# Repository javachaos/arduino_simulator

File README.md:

# arduino_simulator

`arduino_simulator` is a standalone AVR simulation and board-tooling workspace.

https://javachaos.github.io/arduino_simulator/

## License

This workspace is licensed under the GNU General Public License, version 3
or later. See `LICENSE`.

## Current Layout

The workspace is now split cleanly by responsibility:

- `rust_cpu/`
  Native AVR instruction-set simulator
- `rust_mcu/`
  Native ATmega328P / ATmega2560 MMIO and board-facing runtime layers
- `rust_board/`
  Native board DSL, KiCad import, and layout geometry
- `rust_project/`
  Native document model for projects, boards, modules, and hierarchical assemblies
- `rust_behavior/`
  Native declarative behavior definitions plus compiled runtime behavior engines for reusable modules
- `rust_runtime/`
  Native CLI for running Mega/Nano firmware from Intel HEX
- `rust_gui/`
  Native desktop GUI for compile/load/run plus CPU and serial inspection
- `rust_kicad/`
  Native KiCad adapter for generating/syncing `.avrsim.json` projects from KiCad PCBs
- `kicad_plugin/`
  Thin KiCad PCB action plugin that launches the Rust KiCad adapter from inside PCB Editor

The checked-in workspace is Rust-only. Board parsing, built-in models, layout
geometry, and document formats now live in the Rust crates.

## Native Runtime

Run Nano firmware:

```sh
cargo run -p rust_runtime -- run-nano /path/to/firmware.hex
```

Run Mega firmware:

```sh
cargo run -p rust_runtime -- run-mega /path/to/firmware.hex
```

Launch the native terminal monitor:

```sh
cargo run -p rust_runtime -- monitor-mega /path/to/firmware.hex
```

## Native GUI

Launch the desktop GUI:

```sh
cargo run -p rust_gui
```

The GUI can:

- compile an Arduino `.ino` sketch with `arduino-cli`
- load a `.hex` image directly
- open and save simulation project JSON documents
- open a dedicated board editor for authoring multi-PCB board-stack files
- keep the selected host board, firmware source, and PCB path together
- load board-definition JSON documents and render their primary PCB-backed member directly
- edit and persist host signal to PCB net bindings
- load multiple PCB-backed board/module members into one assembly bundle
- associate optional `Mega` / `Nano` host boards plus `.ino` / `.hex` firmware per member
- associate built-in or file-backed runtime behaviors with reusable sensor/interface modules
- wire member ports together and save the result as an `assembly_bundle` board file
- open a bidirectional serial console window with host baud selection
- run, pause, step, reset, and clear serial output
- show CPU state, registers, next instruction, compile log, and scrollable serial output

The GUI and project crates use `rust_board` for KiCad import, built-in board
models, and layout rendering.

For the least-friction auto-wiring and live net highlighting, keep your PCB net
names aligned with the selected Arduino board. In practice that means using the
same Arduino-facing signal names where possible, such as `D22`, `D50_MISO`, or
`A10`, or the official MCU-port names used by that board design, such as
`PA0`, `PC6`, or `PK2` on a Mega 2560.

## KiCad Plugin

If you want one-click launch behavior from KiCad PCB Editor, install the action
plugin:

```sh
python3 /Users/fred/Documents/arduino_simulator/kicad_plugin/install_kicad_plugin.py
```

Then use:

- `Tools -> External Plugins -> Open Arduino Simulator`

The plugin now offers:

- `Generic PCB mode` for opening any KiCad board directly in the GUI
- `Arduino simulation project` mode for `.avrsim.json` generation, firmware,
  and host-board binding workflows

## Rust Workspace

Run the native test suites from the workspace root:

```sh
cargo test -p rust_cpu
cargo test -p rust_mcu
cargo test -p rust_board
cargo test -p rust_project
cargo test -p rust_runtime
cargo test -p rust_gui
cargo test -p rust_kicad
```

Or run everything:

```sh
cargo test
```

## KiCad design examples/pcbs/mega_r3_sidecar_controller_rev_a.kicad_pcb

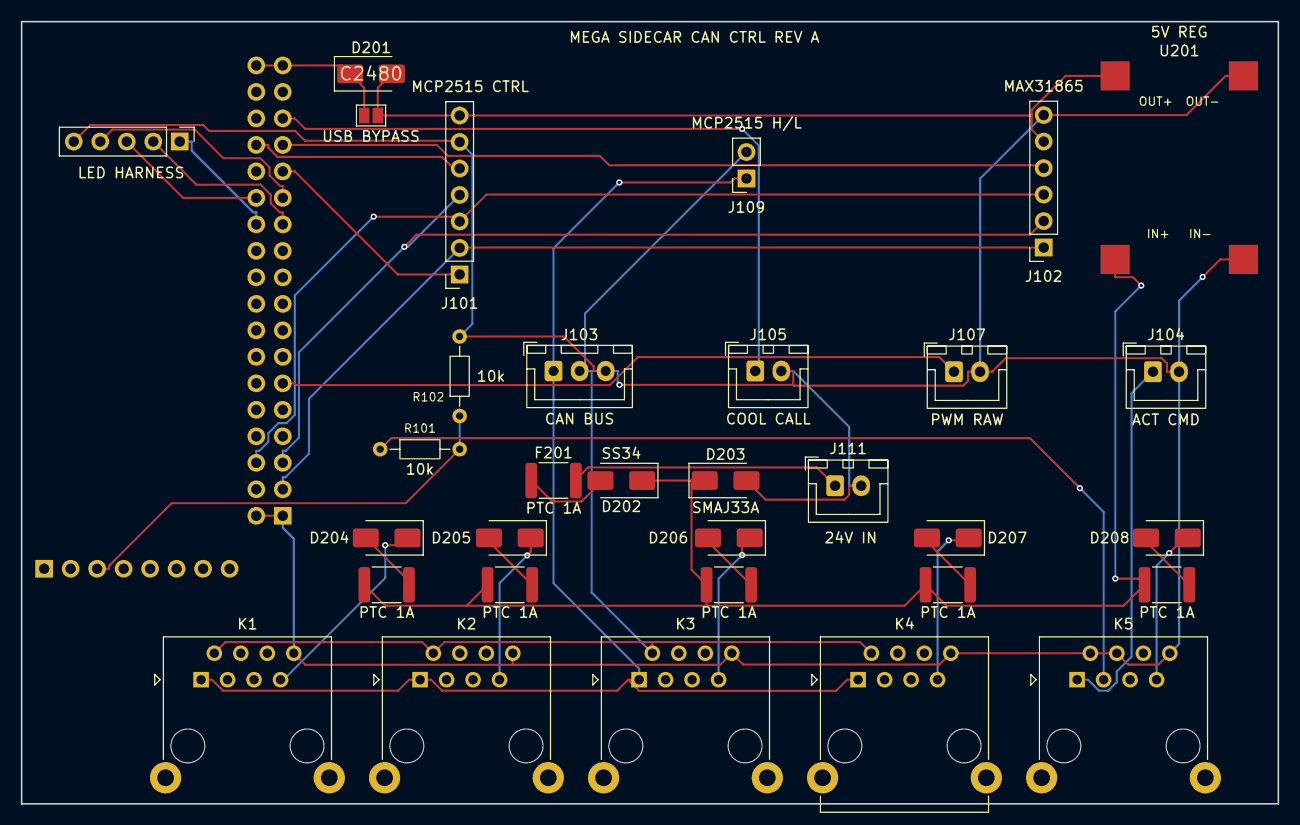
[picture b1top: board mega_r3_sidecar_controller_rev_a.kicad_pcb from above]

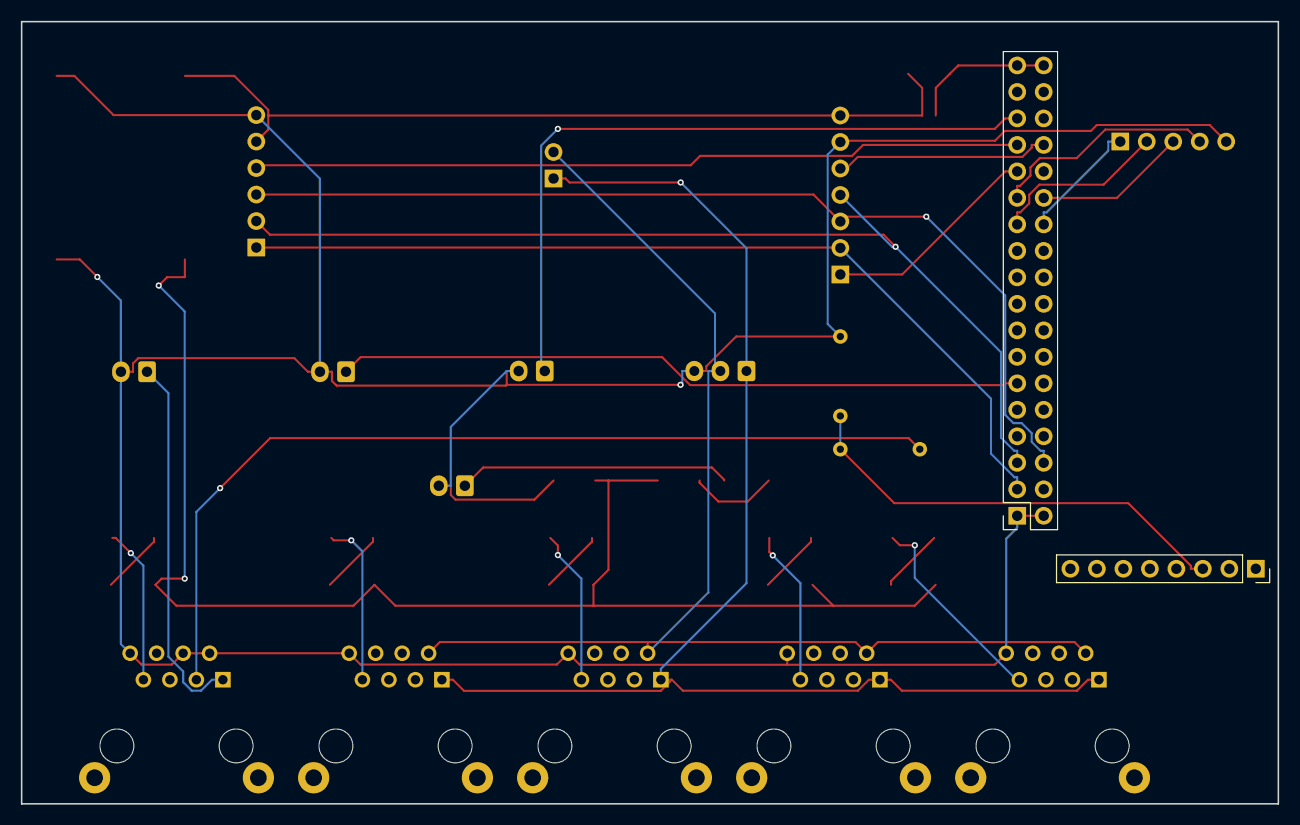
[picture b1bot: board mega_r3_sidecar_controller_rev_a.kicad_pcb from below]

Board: 2 copper layers, 120.5 x 75.0 mm, 34 parts (2 on the bottom side), 33 nets.

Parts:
D201, D204, D205, D206, D207, D208: SS14; D_SMA
D202: SS34; D_SMA
D203: SMAJ33A; D_SMA
F201, F202, F203, F204, F205, F206: PTC 1A; Fuse_1812_4532Metric
J101: MCP2515 CTRL; PinSocket_1x07_P2.54mm_Vertical
J102: MAX31865; PinSocket_1x06_P2.54mm_Vertical
J103: CAN BUS; JST_XH_B3B-XH-A_1x03_P2.50mm_Vertical
J104: ACT CMD; JST_XH_B2B-XH-A_1x02_P2.50mm_Vertical
J105: COOL CALL; JST_XH_B2B-XH-A_1x02_P2.50mm_Vertical
J106: LED HARNESS; PinHeader_1x05_P2.54mm_Vertical
J107: PWM RAW; JST_XH_B2B-XH-A_1x02_P2.50mm_Vertical
J109: MCP2515 H/L; PinSocket_1x02_P2.54mm_Vertical
J111: 24V IN; JST_XH_B2B-XH-A_1x02_P2.50mm_Vertical
K1: AIR Z1; RJ45_RCH_RC01937
K2: AIR Z2; RJ45_RCH_RC01937
K3: AIR Z3; RJ45_RCH_RC01937
K4: AIR SPARE; RJ45_RCH_RC01937
K5: ACTUATOR; RJ45_RCH_RC01937
P_AUX: MEGA A8-A15; PinHeader_1x08_P2.54mm_Vertical
P_DIG: MEGA D22-D53; PinHeader_2x18_P2.54mm_Vertical
R101, R102: 10k; R_Axial_DIN0204_L3.6mm_D1.6mm_P7.62mm_Horizontal
SJ201: USB BYPASS; SolderJumper-2_P1.3mm_Open_Pad1.0x1.5mm
U201: 5V REG MOD; Regulator_Module_12.3x17.6mm

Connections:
+5V: D201.2, J101.7, J102.5, SJ201.2, U201.3
/ACT_U_RAW: K5.3, R101.1
/ADC10: P_AUX.3, R101.2, R102.1
/PA3: J105.1, P_DIG.31
/PA4: J101.5, P_DIG.30
/PA5: J102.4, P_DIG.29
/PA7: J101.1, P_DIG.27
/PB0: J101.2, J102.1, P_DIG.3
/PB2: J101.4, J102.2, P_DIG.5
/PB3: J101.3, J102.3, P_DIG.6
/PC4: J106.2, P_DIG.23
/PC5: J106.1, P_DIG.24
/PC6: J106.4, P_DIG.25
/PC7: J106.3, P_DIG.26
/PL4: J107.1, P_DIG.11
ACT_Y_CMD: J104.1, K5.1
CANH: J103.1, J109.1, K1.1, K2.1, K3.1, K4.1
CANL: J103.2, J109.2, K1.2, K2.2, K3.2, K4.2
FIELD_24V: D202.1, D203.1, F202.1, F203.1, F204.1, F205.1, F206.1, U201.1
GND: D203.2, J101.6, J102.6, J103.3, J104.2, J105.2, J106.5, J107.2, J111.2, K1.8, K2.8, K3.8, K4.8, K5.2, K5.4, K5.8, P_DIG.1, P_DIG.2, R102.2, U201.2, U201.4
K1_24V: D204.1, K1.7
K1_24V_FUSED: D204.2, F202.2
K2_24V: D205.1, K2.7
K2_24V_FUSED: D205.2, F203.2
K3_24V: D206.1, K3.7
K3_24V_FUSED: D206.2, F204.2
K4_24V: D207.1, K4.7
K4_24V_FUSED: D207.2, F205.2
K5_24V: D208.1, K5.7
K5_24V_FUSED: D208.2, F206.2
MEGA_5V: D201.1, P_DIG.35, P_DIG.36, SJ201.1
VIN_FUSED_24V: D202.2, F201.1
VIN_RAW_24V: F201.2, J111.1

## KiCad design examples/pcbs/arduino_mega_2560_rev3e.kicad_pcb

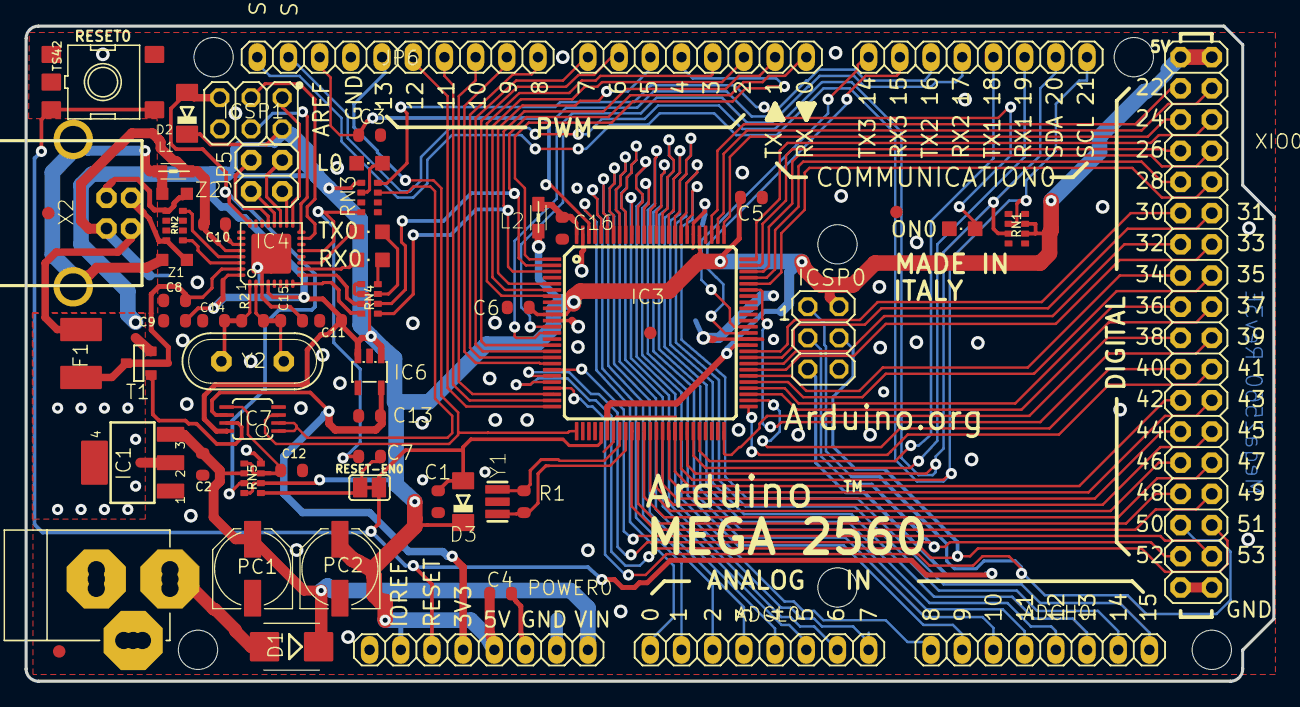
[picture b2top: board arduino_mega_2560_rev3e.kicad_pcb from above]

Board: 2 copper layers, 101.6 x 53.3 mm, 72 parts (1 on the bottom side), 111 nets.

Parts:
ADCH0: FH254-108DF08500V; 1X08
ADCL0: FH254-108DF08500V; 1X08
C1, C14, C15: 22p; C0603-ROUND
C2, C3, C4, C5, C6, C7, C8, C9, C11, C12, C16: 100nF; C0603-ROUND
C10, C13: 1uF; C0603-ROUND
COMMUNICATION0: FH254-108DF08500V; 1X08
D1: M7; SMB
D2, D3: CD1206-S01575; MINIMELF
F1: MF-MSMF050-2 500mA; L1812
FD1, FD2, FD3, FD4: FIDUCIALMOUNT; FIDUCIA-MOUNT
GROUND0: SJ
IC1: 1870_LD1117S50CTR; LINEAR_SOT223
IC3: ATMEGA2560-15AU; TQFP100
IC4: ATMEGA16U2-MU; MLF32
IC6: LP2985-33DBVR; SOT23-DBV
IC7: LMV358IDGKR; MSOP08
ICSP0, ICSP1: ICSP; 2X03
JP5: 2x2M - NM; 2X02
JP6: FH254-110DF08500V; 1X10
L0: Yellow; CHIPLED_0805
L1: MH2029-300Y; 0805
L2: 10uH; 0805
ON0: Green; CHIPLED_0805
PC1, PC2: 47uF; PANASONIC_D
POWER0: FH254-108DF08500V; 1X08
PWML0: FH254-108DF08500V; 1X08
R1, R2: 1M; R0603-ROUND
RESET0: TS42
RESET-EN0: SJ
RN1, RN5: 10k; CAY16
RN2: 22R; CAY16
RN3, RN4: 1K; CAY16
RX0: Yellow; CHIPLED_0805
T1: PMV48XP; SOT-23
TX0: Yellow; CHIPLED_0805
U$1, U$2: DNP; FRAME
UNK_HOLE_0: dummyfp0
UNK_HOLE_1: dummyfp1
UNK_HOLE_2: dummyfp2
UNK_HOLE_3: dummyfp3
UNK_HOLE_4: dummyfp4
UNK_HOLE_5: dummyfp5
X1: POWERSUPPLY_DC21MMX; POWERSUPPLY_DC-21MM
X2: PN61729
XIO0: 18x2F-H8.5; 2X18
Y1: CSTCE16M0V53-R0; RESONATOR
Y2: 16MHz; QS
Z1, Z2: BRNCG0603MLC-05E; CT_CN0603

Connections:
8PB4: IC4.18, JP5.1
8PB5: IC4.19, JP5.3
8PB6: IC4.20, JP5.2
8PB7: IC4.21, JP5.4
+3V3: C13.2, IC6.5, IC7.6, POWER0.4
+5V: C4.1, C5.1, C6.1, C9.1, C11.2, D2.C, D3.C, IC1.2, IC1.4, IC3.10, IC3.31, IC3.61, IC3.80, IC4.4, IC4.32, IC6.1, IC6.3, IC7.8, ICSP0.2, ICSP1.2, L2.2, PC2.+, POWER0.2, POWER0.5, RN1.6, RN1.7, RN3.1, RN4.5, RN4.6, RN5.2, RN5.8, T1.2, XIO0.1, XIO0.2
ADC0: ADCL0.1, IC3.97
ADC1: ADCL0.2, IC3.96
ADC2: ADCL0.3, IC3.95
ADC3: ADCL0.4, IC3.94
ADC4: ADCL0.5, IC3.93
ADC5: ADCL0.6, IC3.92
ADC6: ADCL0.7, IC3.91
ADC7: ADCL0.8, IC3.90
ADC8: ADCH0.1, IC3.89
ADC9: ADCH0.2, IC3.88
ADC10: ADCH0.3, IC3.87
ADC11: ADCH0.4, IC3.86
ADC12: ADCH0.5, IC3.85
ADC13: ADCH0.6, IC3.84
ADC14: ADCH0.7, IC3.83
ADC15: ADCH0.8, IC3.82
AREF: C3.1, IC3.98, JP6.3
AVCC: C16.1, IC3.100, L2.1
CMP: C12.2, IC7.5, RN5.3, RN5.5
D+: RN2.5, X2.3, Z2.2
D-: RN2.8, X2.2, Z1.2
DTR: C7.1, IC4.13, RN3.4
GATE_CMD: IC7.7, T1.3
GND: C1.2, C2.2, C3.2, C4.2, C5.2, C6.2, C8.2, C9.2, C11.1, C12.1, C13.1, C14.2, C15.2, C16.2, GROUND0.2, IC1.1, IC3.11, IC3.32, IC3.62, IC3.81, IC3.99, IC4.3, IC4.33, IC6.2, IC7.4, ICSP0.6, ICSP1.6, JP6.4, L0.C, ON0.C, PC1.-, PC2.-, POWER0.6, POWER0.7, RESET0.1, RESET0.2, RN3.5, RN5.4, X1.1, X1.3, XIO0.35, XIO0.36, Y1.2
L13: IC7.1, IC7.2, RN3.7
M8RXD: IC4.9, RN4.7
M8TXD: IC4.8, RN4.8
MISO2: IC4.17, ICSP1.1
MOSI2: IC4.16, ICSP1.4
unnamed: L0.A, RN3.2
unnamed: ON0.A, RN3.8
unnamed: RN4.4, RX0.A
unnamed: RN4.3, TX0.A
PA0: IC3.78, XIO0.3
PA1: IC3.77, XIO0.4
PA2: IC3.76, XIO0.5
PA3: IC3.75, XIO0.6
PA4: IC3.74, XIO0.7
PA5: IC3.73, XIO0.8
PA6: IC3.72, XIO0.9
PA7: IC3.71, XIO0.10
PB0: IC3.19, XIO0.34
PB1: IC3.20, ICSP0.3, XIO0.33
PB2: IC3.21, ICSP0.4, XIO0.32
PB3: IC3.22, ICSP0.1, XIO0.31
PB4: IC3.23, JP6.8
PB5: IC3.24, JP6.7
PB6: IC3.25, JP6.6
PB7: IC3.26, IC7.3, JP6.5
PC0: IC3.53, XIO0.18
PC1: IC3.54, XIO0.17
PC2: IC3.55, XIO0.16
PC3: IC3.56, XIO0.15
PC4: IC3.57, XIO0.14
PC5: IC3.58, XIO0.13
PC6: IC3.59, XIO0.12
PC7: IC3.60, XIO0.11
PD7: IC3.50, XIO0.19
PE0: IC3.2, PWML0.1, RN4.2
PE1: IC3.3, PWML0.2, RN4.1
PE3: IC3.5, PWML0.6
PE4: IC3.6, PWML0.3
PE5: IC3.7, PWML0.4
PG0: IC3.51, XIO0.22
PG1: IC3.52, XIO0.21
PG2: IC3.70, XIO0.20
PG5: IC3.1, PWML0.5
PH3: IC3.15, PWML0.7
PH4: IC3.16, PWML0.8
PH5: IC3.17, JP6.10
PH6: IC3.18, JP6.9
PL0: IC3.35, XIO0.30
PL1: IC3.36, XIO0.29
PL2: IC3.37, XIO0.28
PL3: IC3.38, XIO0.27
PL4: IC3.39, XIO0.26
PL5: IC3.40, XIO0.25
PL6: IC3.41, XIO0.24
PL7: IC3.42, XIO0.23
PWRIN: D1.A, X1.2
RD+: IC4.29, RN2.4
RD-: IC4.30, RN2.1
RESET: C1.1, C7.2, D3.A, IC3.30, ICSP0.5, POWER0.3, RESET0.3, RESET0.4, RESET-EN0.1, RESET-EN0.2, RN5.1
RESET2: D2.A, IC4.24, ICSP1.5, RN5.7
RXD1: COMMUNICATION0.3, IC3.45
RXD2: COMMUNICATION0.5, IC3.12
RXD3: COMMUNICATION0.7, IC3.63
RXL: IC4.10, RX0.C
SCK2: IC4.15, ICSP1.3
SCL: COMMUNICATION0.1, IC3.43, JP6.1, RN1.2
SDA: COMMUNICATION0.2, IC3.44, JP6.2, RN1.3
TXD1: COMMUNICATION0.4, IC3.46
TXD2: COMMUNICATION0.6, IC3.13
TXD3: COMMUNICATION0.8, IC3.64
TXL: IC4.11, TX0.C
UGND: C10.2, GROUND0.1, IC4.28, L1.1, X2.4
USBVCC: C8.1, F1.1, IC4.31, T1.1
USHIELD: L1.2, X2.P$1, X2.P$2, Z1.1, Z2.1
VIN: C2.1, D1.C, IC1.3, PC1.+, POWER0.8, RN5.6
VUCAP: C10.1, IC4.27
XT1: C14.1, IC4.1, R2.1, Y2.2
XT2: C15.1, IC4.2, R2.2, Y2.1
XTAL1: IC3.34, R1.1, Y1.3
XTAL2: IC3.33, R1.2, Y1.1
XVCC: F1.2, X2.1

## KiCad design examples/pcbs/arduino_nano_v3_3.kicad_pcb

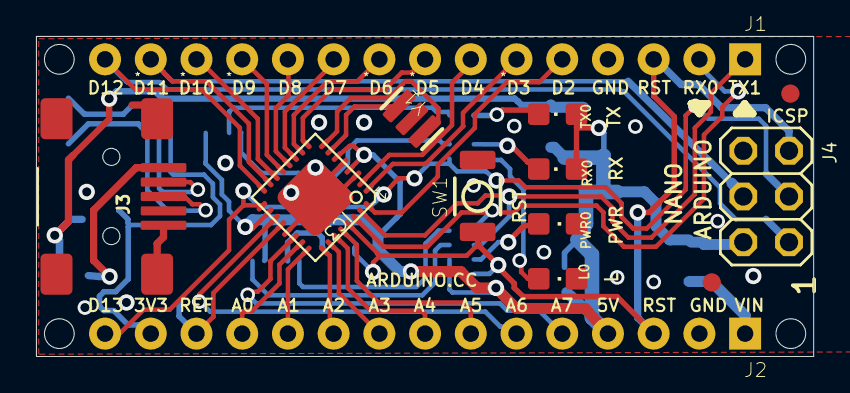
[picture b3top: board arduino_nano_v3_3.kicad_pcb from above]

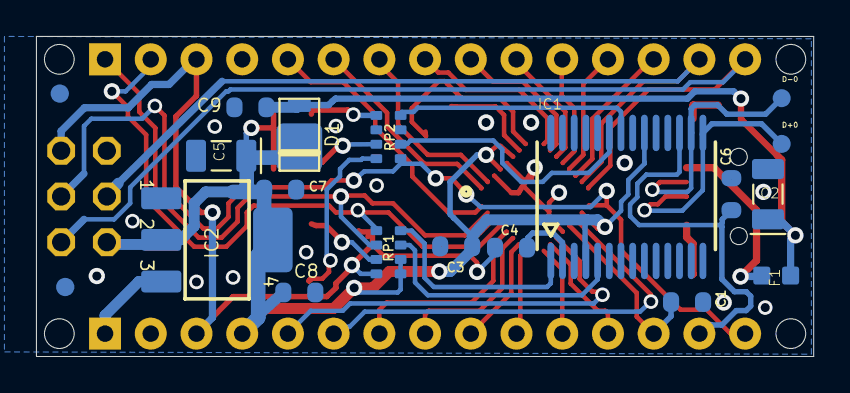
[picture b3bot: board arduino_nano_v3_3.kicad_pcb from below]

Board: 2 copper layers, 43.2 x 17.8 mm, 37 parts (17 on the bottom side), 43 nets.

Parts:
C1, C4, C6, C9: 100nF; C0603-ROUND
C2, C5: 4,7uF_16V; TAN-A
C3, C7, C8: 1uF; C0603-ROUND
D1: SS1P3L; DO220AAL
D+0: DNP; TP-1.00MM
D-0: DNP; TP-1.00MM
F1: MFFSMF050; 0603-1608X90N
FRAME1: DNP; FRAME
IC1: FT232RL; SSOP28
IC2: LM1117IMPX-5.0; LINEAR_SOT223
IC3: 328P-MUR; VQFN32
J1, J2: XXXX_STRIPNANO; HEAD15-NOSS
J3: USB-MINI-B_2
J4: 2X03
L0: Yellow; CHIPLED_0805
PWR0: Green; CHIPLED_0805
RP1, RP2: 1K; CAY16
RX0: Red; CHIPLED_0805
SW1: RESET; SMD_157SW
TX0: Green; CHIPLED_0805
U$4, U$5, U$53, U$54: DNP; FD-1-1.5
UNK_HOLE_0: dummyfp0
UNK_HOLE_1: dummyfp1
UNK_HOLE_2: dummyfp2
UNK_HOLE_3: dummyfp3
Y1: 16MHz; RESONATOR

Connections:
3V3: C6.2, IC1.17, J2.14
+5V: C3.1, C5.1, C7.1, C8.1, D1.P$1, IC1.4, IC1.20, IC2.2, IC2.4, IC3.4, IC3.6, IC3.18, J2.4, J4.2, RP1.5, RP1.6, RX0.A, TX0.A
A0: IC3.23, J2.12
A1: IC3.24, J2.11
A2: IC3.25, J2.10
A3: IC3.26, J2.9
A4: IC3.27, J2.8
A5: IC3.28, J2.7
A6: IC3.19, J2.6
A7: IC3.22, J2.5
AREF: C1.1, IC3.20, J2.13
COM: C1.2, C2.2, C3.2, C5.2, C6.1, C7.2, C8.2, C9.2, IC1.7, IC1.18, IC1.21, IC1.25, IC1.26, IC2.1, IC3.3, IC3.5, IC3.21, IC3.33, J1.4, J2.2, J3.1, J3.6, J3.7, J3.8, J3.9, J4.6, L0.C, PWR0.C, RP2.3, RP2.6, SW1.1, Y1.2
D0/RX: IC3.30, J1.2, RP1.1
D1/TX: IC3.31, J1.1, RP1.2
D2: IC3.32, J1.5
D3: IC3.1, J1.6
D4: IC3.2, J1.7
D5: IC3.9, J1.8
D6: IC3.10, J1.9
D7: IC3.11, J1.10
D8: IC3.12, J1.11
D9: IC3.13, J1.12
D10: IC3.14, J1.13
D11/MOSI: IC3.15, J1.14, J4.4
D12/MISO: IC3.16, J1.15, J4.1
D13/SCK: IC3.17, J2.15, J4.3, RP2.1
unnamed: IC3.8, Y1.3
unnamed: IC3.7, Y1.1
unnamed: PWR0.A, RP1.3
unnamed: C4.2, IC1.2
unnamed: D+0.X, IC1.15, J3.3
unnamed: D-0.X, IC1.16, J3.4
unnamed: L0.A, RP2.8
unnamed: IC1.23, RP2.2
unnamed: IC1.22, RP2.4
unnamed: RP2.5, TX0.C
unnamed: F1.2, J3.5
unnamed: RP2.7, RX0.C
RESET: C4.1, IC3.29, J1.3, J2.3, J4.5, RP1.4, SW1.2
RX: IC1.1, RP1.8
TX: IC1.5, RP1.7
VIN: IC2.3, J2.1
VUSB: C2.1, C9.1, D1.P$2, F1.1

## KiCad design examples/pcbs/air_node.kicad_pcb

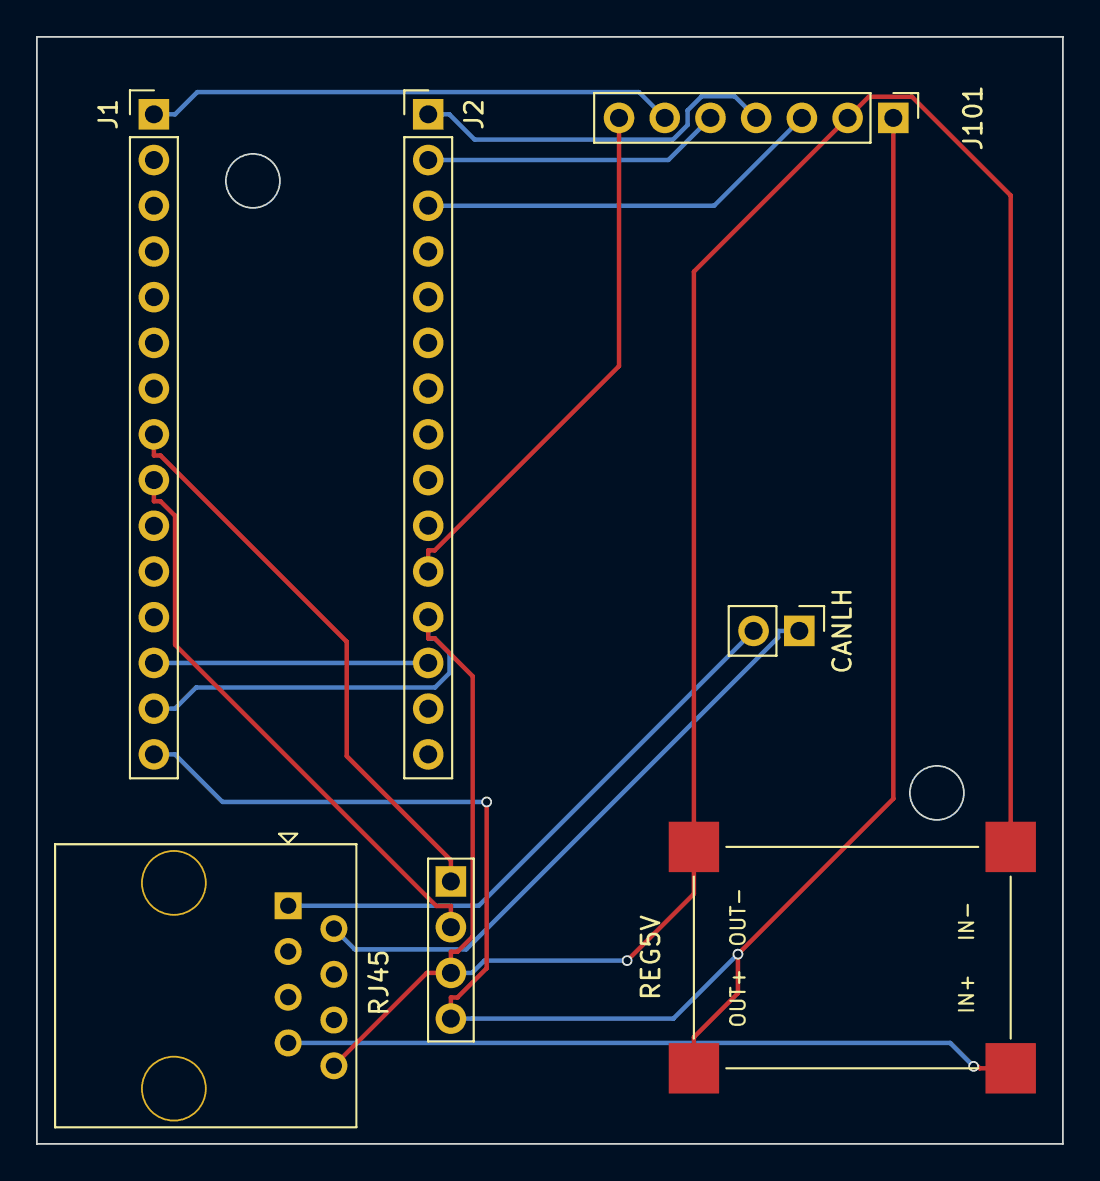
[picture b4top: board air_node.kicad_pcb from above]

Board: 2 copper layers, 57.0 x 61.5 mm, 7 parts (0 on the bottom side), 13 nets.

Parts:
CANLH: PinHeader_1x02_P2.54mm_Vertical
J1, J2: NANO; PinHeader_1x15_P2.54mm_Vertical
J101: PinHeader_1x07_P2.54mm_Vertical
REG5V: Regulator_Module_12.3x17.6mm
RJ45: RJ45_OST_PJ012-8P8CX_Vertical
SHT31: Pins_1x04_2.54mm_TH

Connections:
+24V: REG5V.1, RJ45.7
/*D10/SS: J2.3, J101.3
/*D11/MOSI: J2.2, J101.5
/A4/SDA: J1.8, SHT31.1
/A5/SCL: J1.9, SHT31.2
/D2: J2.11, J101.7
/D12/MISO: J2.1, J101.4
/D13/SCK: J1.1, J101.6
/~RESET: J1.13, J2.13
CAN_H: CANLH.2, RJ45.1
CAN_L: CANLH.1, RJ45.2
GND: J1.14, J2.12, J101.2, REG5V.2, REG5V.4, RJ45.8, SHT31.3
VCC: J1.15, J101.1, REG5V.3, SHT31.4

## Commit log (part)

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2026-03-26 Remove Python tooling and rename workspace to arduino_simulator
2026-03-26 Rename Cargo binaries to arduino-simulator
2026-03-26 Rename avrsim, remove Python, and save project paths relatively
2026-03-26 Improve PCB wiring suggestions and collapsible pin panel
2026-03-26 Refactor builtins and expand board wiring and module support
2026-03-27 Normalize Arduino net aliases across wiring and preview UI
2026-03-27 Expand rust_cpu instruction and API coverage tests
2026-03-27 Expand coverage tests and add Mega pin sweep sketch
2026-03-27 Improve coverage tooling and fix GUI board retargeting
2026-03-27 Add web simulator with KiCad board preview and serial console
2026-03-27 renamed pages folder
2026-03-27 Include project documentation URL in README
    Add project documentation link to README
2026-04-02 Revise README to streamline content
    Removed unnecessary details about the crate's focus and compilation status.
2026-04-02 Add KiCad plugin packaging and release workflow
2026-04-02 Fix GitHub release asset discovery
2026-04-02 Fix gh release job repo detection
2026-04-02 Update simulator changes
2026-04-02 Fixed simulated CPU pacing issue
2026-04-06 Add serializable simulator core and input controls
2026-04-22 Bump rand from 0.8.5 to 0.8.6
    Bumps [rand](https://github.com/rust-random/rand) from 0.8.5 to 0.8.6.
    - [Release notes](https://github.com/rust-random/rand/releases)
    - [Changelog](https://github.com/rust-random/rand/blob/0.8.6/CHANGELOG.md)
    - [Commits](https://github.com/rust-random/rand/compare/0.8.5...0.8.6)
    ---
    updated-dependencies:
2026-05-15 Add AVR decoded instruction cache
